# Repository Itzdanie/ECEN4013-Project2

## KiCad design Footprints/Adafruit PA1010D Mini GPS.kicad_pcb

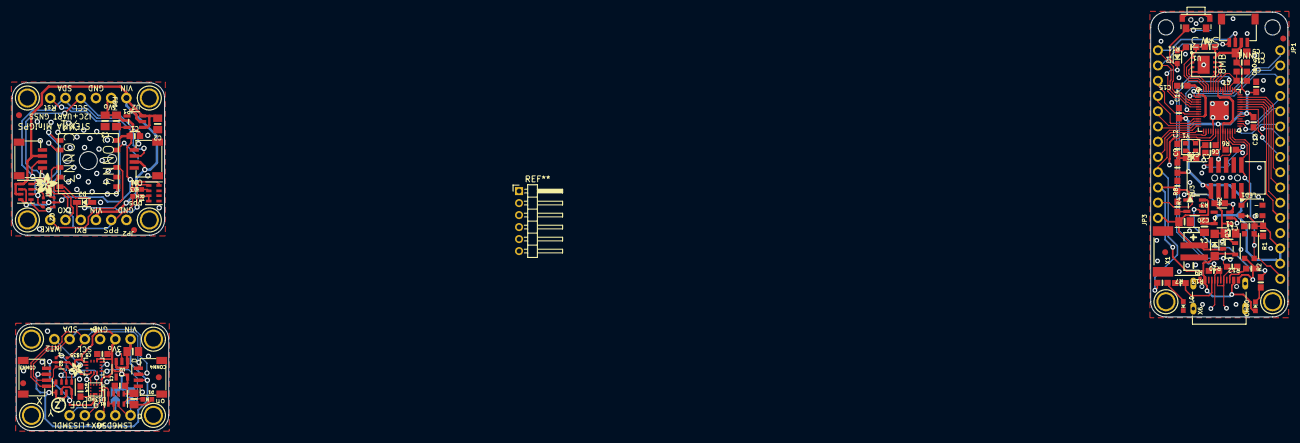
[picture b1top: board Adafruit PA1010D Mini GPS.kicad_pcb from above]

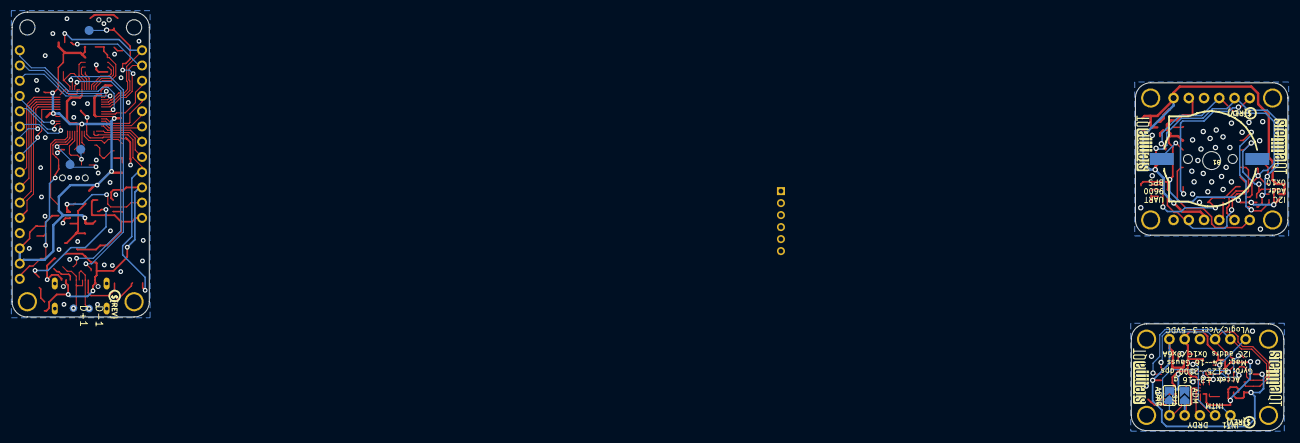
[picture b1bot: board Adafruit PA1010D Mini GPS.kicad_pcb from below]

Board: 2 copper layers, 212.6 x 69.7 mm, 118 parts (16 on the bottom side), 71 nets.

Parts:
@HOLE0, @HOLE1: (no value)
B1: CR1220-2
C1, C1#2, C4#2, C6, C7, C9, C11, C12, C13, C14, C15, C16: 0.1uF; 0603-NO
C1#3, C2, C2#2, C3, C3#2, C4, C5, C20: 10uF; 0805-NO
C2#3, C3#3: 22pF; 0603-NO
C5#2, C8, C10: 1uF; 0603-NO
CHG0: ORANGE; CHIPLED_0603_NOOUTLINE
CONN1, CONN3, CONN3#2, CONN4, CONN4#2: STEMMA_I2C_QT; JST_SH4
D1, D1#2: GREEN; CHIPLED_0603_NOOUTLINE
D1#3: NSR0320; SOD-323_MINI
D2: 1N4148; SOD-323
D3: RED; CHIPLED_0603_NOOUTLINE
D4: MBR0540; SOD-123
D+1: TPB1,27; B1,27_385
D-1: TPB1,27; B1,27_385
FB1: FERRITE; 0805-NO
FID3, FID3#2, FID4, FID4#2: FIDUCIAL_1MM
IC1: RP2040_QFN56; QFN56_7MM_REDUCEDEPAD
IC1#2: LIS3MDL; LGA12_2X2MM
JP1: 1X05_ROUND_70
JP1#2: 1X16_ROUND
JP1#3, JP2, JP4: 1X06_ROUND_70
JP3: 1X12_ROUND
L0: RED; CHIPLED_0603_NOOUTLINE
LED1: WS2812B3535; LED3535
Q2, Q2#2: BSS138; SOT363
Q3: DMG3415; SOT23-R
R1, R2, R3, R4, R5, R7: 10K; 0603-NO
R1#2, R1#3, R3#2, R3#3: 10K; RESPACK_4X0603
R6, R11: 1K; 0603-NO
R8, R12, R13: 5.1K; 0603-NO
R9, R10: 27; 0603-NO
SJ1, SJ2: SOLDERJUMPER_ARROW_NOPASTE
SW1: KMR2; BTN_KMR2_4.6X2.8
SW3: Mini RA Switch; SPST_TACTILE_RA_2*4*3.5MM
TP1, TP2, TP3: TESTPOINT_ROUND_1.5MM_NO
U1: W25Q64JVSSIQ; USON8_4X4
U2: RT9080/AP2112-3.3; SOT23-5
U2#2, U2#3: AP2112K-3.3; SOT23-5
U3: MCP73831T-2ACI/OT; SOT23-5
U$1, U$1#2, U$17, U$17#2, U$19, U$19#2, U$21, U$21#2, U$31, U$32: MOUNTINGHOLE2.5; MOUNTINGHOLE_2.5_PLATED
U$1#3: RP2040_BOT
U$13, U$25, U$25#2: PCBFEAT-REV-040
U$20: ADAFRUIT_2.5MM
U$22: ADAFRUIT_3.5MM
U$30, U$30#2, U$31#2, U$31#3: STEMMAQT
U$34, U$35#2: FIDUCIAL_1MM
U$35: LSM6DSOX; LGA-14L
U$43: RP2040_TOP
X1: JSTPH; JSTPH2_BATT
X1#2: GPS_PA1010D
X2: 2x5 SWD; 2X05_1.27MM_BOX_NOCREAM
X6: USB Type C; USB_C_CUSB31-CFM2AX-01-X
Y1: 12MHz/12pF; CRYSTAL_2.5X2

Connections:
1.2V: C6.2, C7.2, C8.1, IC1.23, IC1.45, IC1.50
1PPS: D3.A, JP2.2, X1#2.3
3.3V: C1.1, C1#2.1, C3.1, C3#2.1, C5#2.1, D1.A, FB1.2, IC1#2.5, IC1#2.6, IC1#2.10, JP1#3.2, JP4.2, Q2.2, Q2.5, Q2#2.2, Q2#2.5, R1#2.1, R1#3.4, R3#2.2, R3#2.4, R3#3.2, R3#3.4, SJ1.2, SJ2.2, U2#3.5, U$35.5, U$35.8, U$35.12, X1#2.10
+3V3: C4.1, C5.1, C9.1, C10.1, C11.1, C12.1, C13.1, C14.1, C15.1, C16.1, CONN1.2, IC1.1, IC1.10, IC1.22, IC1.33, IC1.42, IC1.43, IC1.44, IC1.48, IC1.49, JP1#2.14, JP1#2.15, LED1.2, R1.1, R5.2, U1.8, U2.5, X2.1
A0: IC1.38, JP1#2.12
A1: IC1.39, JP1#2.11
A2: IC1.40, JP1#2.10
A3: IC1.41, JP1#2.9
ADAG: JP1.1, R1#2.7, SJ2.1, U$35.1
ADM: IC1#2.9, JP1.2, R1#2.4, R1#2.5, R1#2.6, SJ1.1
CAP: C4#2.1, IC1#2.4
CC1: R13.2, X6.A5
CC2: R12.2, X6.B5
D4: IC1.8, JP1#2.1
D5: IC1.9, JP3.10
D6: IC1.11, JP3.9
D9: IC1.12, JP3.8
D10: IC1.13, JP3.7
D11: IC1.14, JP3.6
D12: IC1.15, JP3.5
D13: IC1.16, JP3.4, R7.1
D24: IC1.36, JP1#2.8
D25: IC1.37, JP1#2.7
D+: IC1.47, R10.2
D-: IC1.46, R9.2
DRDY: IC1#2.8, JP1.3
EN: JP3.2, R3.1, U2.3
GND: B1.-, C1.2, C1#2.2, C1#3.2, C2.2, C2#2.2, C2#3.1, C3.2, C3#2.2, C3#3.1, C4.2, C4#2.2, C5.2, C5#2.2, C6.1, C7.1, C8.2, C9.2, C10.2, C11.2, C12.2, C13.2, C14.2, C15.2, C16.2, C20.2, CONN1.1, CONN1.MT1, CONN1.MT2, CONN3.1, CONN3.MT1, CONN3.MT2, CONN3#2.1, CONN4.1, CONN4.MT1, CONN4.MT2, CONN4#2.1, D1#2.C, IC1.19, IC1.P$1, IC1#2.2, IC1#2.3, IC1#2.12, JP1#2.13, JP1#3.3, JP2.1, JP4.3, L0.C, LED1.4, R1#2.2, R1#2.3, R1#3.1, R1#3.2, R1#3.3, R4.1, R8.2, R12.1, R13.1, SW1.B, SW1.B', SW3.1, SW3.MT1, SW3.MT2, U1.4, U1.PAD, U2.2, U2#2.2, U2#3.2, U3.2, U$35.6, U$35.7, X1.1, X1.NC1, X1.NC2, X1#2.7, X2.3, X2.5, X2.7, X2.9, X6.A1B12, X6.B1A12
INT1: JP1.5, U$35.4
INT2: JP4.6, U$35.9
INTM: IC1#2.7, JP1.4
MISO: IC1.31, JP1#2.4
MOSI: IC1.30, JP1#2.5
unnamed: CHG0.C, D1.C, D1#2.A, R1#2.8, R1#3.6, R2.1
unnamed: D3.C, L0.A, R1#3.7, R1#3.8, R7.2
unnamed: R2.2, U3.1
unnamed: R8.1, U3.5
unnamed: C2#3.2, IC1.20, Y1.3
unnamed: C3#3.2, R6.1, Y1.1
unnamed: IC1.21, R6.2
unnamed: D1#3.A, R11.2
NEOPIX: IC1.27, LED1.1
OUT: FB1.1, U2#2.5
QSPI_CS: IC1.56, R5.1, R11.1, U1.1
QSPI_DATA[0]: IC1.53, U1.5
QSPI_DATA[1]: IC1.55, U1.2
QSPI_DATA[2]: IC1.54, U1.3
QSPI_DATA[3]: IC1.51, U1.7
QSPI_SCK: IC1.52, U1.6
RX: IC1.3, JP1#2.3
RXI: D2.C, JP2.4
RXI_3V: D2.A, R1#3.5, X1#2.5
SCK: IC1.29, JP1#2.6
SCL: CONN1.4, CONN3.4, CONN3#2.4, CONN4.4, CONN4#2.4, IC1.5, JP1#3.4, JP3.11, JP4.4, Q2.6, Q2#2.6, R3#2.8, R3#3.8
SCL_3V: IC1#2.1, Q2.1, Q2#2.1, R3#2.7, R3#3.7, U$35.13, X1#2.2
SDA: CONN1.3, CONN3.3, CONN3#2.3, CONN4.3, CONN4#2.3, IC1.4, JP1#3.5, JP3.12, JP4.5, Q2.3, Q2#2.3, R3#2.6, R3#3.6
SDA_3V: IC1#2.11, Q2.4, Q2#2.4, R3#2.5, R3#3.5, U$35.14, X1#2.1
SWCLK: IC1.24, TP2.P$1, X2.4
SWDIO: IC1.25, TP1.P$1, X2.2
TX: IC1.2, JP1#2.2
TXO: JP2.5, X1#2.4
USBBOOT: D1#3.C, IC1.6, SW3.2, TP3.P$1
USB_D+: D+1.TP, R10.1, X6.A6, X6.B6
USB_D-: D-1.TP, R9.1, X6.A7, X6.B7
VBACKUP: B1.+, X1#2.9
VBAT: C20.1, JP3.1, Q3.3, U3.3, X1.2
VBUS: CHG0.A, D4.A, JP3.3, Q3.1, R4.2, U3.4, X6.A4B9, X6.B4A9
VCC: C2.1, C2#2.1, CONN3.2, CONN3#2.2, CONN4.2, CONN4#2.2, JP1#3.1, JP2.3, JP4.1, R3#2.1, R3#2.3, R3#3.1, R3#3.3, U2#2.1, U2#2.3, U2#3.1, U2#3.3
VHI: C1#3.1, D4.C, Q3.2, R3.2, U2.1
WAKEUP: JP2.6, X1#2.8
~RESET: IC1.26, JP1#2.16, JP1#3.6, R1.2, SW1.A, SW1.A', X1#2.6, X2.10

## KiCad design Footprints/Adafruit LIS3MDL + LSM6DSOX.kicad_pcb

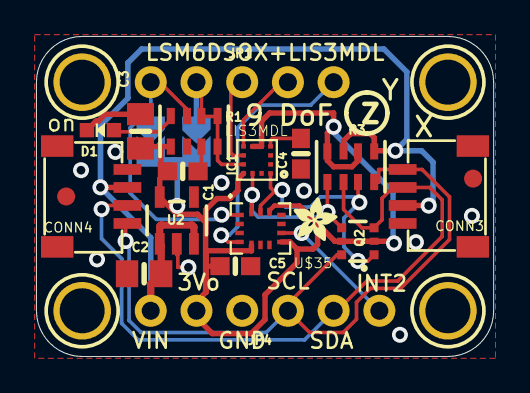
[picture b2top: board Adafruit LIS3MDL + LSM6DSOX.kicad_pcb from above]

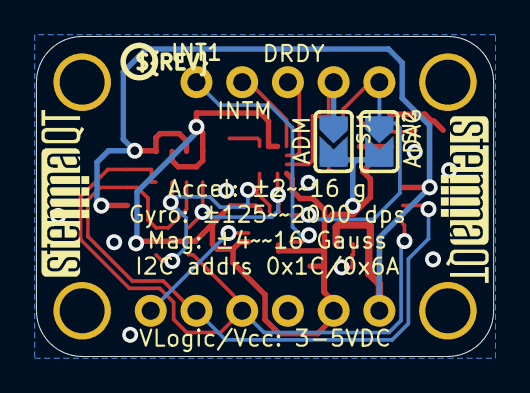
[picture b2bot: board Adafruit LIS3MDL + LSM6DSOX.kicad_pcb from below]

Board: 2 copper layers, 25.4 x 17.8 mm, 28 parts (5 on the bottom side), 15 nets.

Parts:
C1, C4: 0.1uF; 0603-NO
C2, C3: 10uF; 0805-NO
C5: 1uF; 0603-NO
CONN3, CONN4: STEMMA_I2C_QT; JST_SH4
D1: GREEN; CHIPLED_0603_NOOUTLINE
FID3, FID4: FIDUCIAL_1MM
IC1: LIS3MDL; LGA12_2X2MM
JP1: 1X05_ROUND_70
JP4: 1X06_ROUND_70
Q2: BSS138; SOT363
R1, R3: 10K; RESPACK_4X0603
SJ1, SJ2: SOLDERJUMPER_ARROW_NOPASTE
U2: AP2112K-3.3; SOT23-5
U$1, U$17, U$19, U$21: MOUNTINGHOLE2.5; MOUNTINGHOLE_2.5_PLATED
U$20: ADAFRUIT_2.5MM
U$25: PCBFEAT-REV-040
U$30, U$31: STEMMAQT
U$35: LSM6DSOX; LGA-14L

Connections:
3.3V: C1.1, C3.1, C5.1, IC1.5, IC1.6, IC1.10, JP4.2, Q2.2, Q2.5, R1.1, R3.2, R3.4, SJ1.2, SJ2.2, U2.5, U$35.5, U$35.8, U$35.12
ADAG: JP1.1, R1.7, SJ2.1, U$35.1
ADM: IC1.9, JP1.2, R1.4, R1.5, R1.6, SJ1.1
CAP: C4.1, IC1.4
DRDY: IC1.8, JP1.3
GND: C1.2, C2.2, C3.2, C4.2, C5.2, CONN3.1, CONN3.MT1, CONN3.MT2, CONN4.1, CONN4.MT1, CONN4.MT2, D1.C, IC1.2, IC1.3, IC1.12, JP4.3, R1.2, R1.3, U2.2, U$35.6, U$35.7
INT1: JP1.5, U$35.4
INT2: JP4.6, U$35.9
INTM: IC1.7, JP1.4
unnamed: D1.A, R1.8
SCL: CONN3.4, CONN4.4, JP4.4, Q2.6, R3.8
SCL_3V: IC1.1, Q2.1, R3.7, U$35.13
SDA: CONN3.3, CONN4.3, JP4.5, Q2.3, R3.6
SDA_3V: IC1.11, Q2.4, R3.5, U$35.14
VCC: C2.1, CONN3.2, CONN4.2, JP4.1, R3.1, R3.3, U2.1, U2.3
